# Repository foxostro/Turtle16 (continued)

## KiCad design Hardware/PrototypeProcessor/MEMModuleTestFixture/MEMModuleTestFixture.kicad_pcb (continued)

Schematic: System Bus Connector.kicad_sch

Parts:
J2: 71922-164LF; IDC-Header_2x32_P2.54mm_Horizontal

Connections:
/MEM Prototype Inputs/Phi2: J2.55; also elsewhere on the board
/MEM Prototype Inputs/RDY: J2.59; also elsewhere on the board
/MEM Prototype Inputs/~RST_sync: J2.60; also elsewhere on the board
/System Bus Connector/Addr0: J2.7; also elsewhere on the board
/System Bus Connector/Addr1: J2.8; also elsewhere on the board
/System Bus Connector/Addr2: J2.9; also elsewhere on the board
/System Bus Connector/Addr3: J2.10; also elsewhere on the board
/System Bus Connector/Addr4: J2.13; also elsewhere on the board
/System Bus Connector/Addr5: J2.14; also elsewhere on the board
/System Bus Connector/Addr6: J2.15; also elsewhere on the board
/System Bus Connector/Addr7: J2.16; also elsewhere on the board
/System Bus Connector/Addr8: J2.19; also elsewhere on the board
/System Bus Connector/Addr9: J2.20; also elsewhere on the board
/System Bus Connector/Addr10: J2.21; also elsewhere on the board
/System Bus Connector/Addr11: J2.22; also elsewhere on the board
/System Bus Connector/Addr12: J2.25; also elsewhere on the board
/System Bus Connector/Addr13: J2.26; also elsewhere on the board
/System Bus Connector/Addr14: J2.27; also elsewhere on the board
/System Bus Connector/Addr15: J2.28; also elsewhere on the board
/System Bus Connector/Bank0: J2.56; also elsewhere on the board
/System Bus Connector/Bank1: J2.3; also elsewhere on the board
/System Bus Connector/Bank2: J2.4; also elsewhere on the board
/System Bus Connector/IO0: J2.51; also elsewhere on the board
/System Bus Connector/IO1: J2.52; also elsewhere on the board
/System Bus Connector/IO2: J2.49; also elsewhere on the board
/System Bus Connector/IO3: J2.50; also elsewhere on the board
/System Bus Connector/IO4: J2.45; also elsewhere on the board
/System Bus Connector/IO5: J2.46; also elsewhere on the board
/System Bus Connector/IO6: J2.43; also elsewhere on the board
/System Bus Connector/IO7: J2.44; also elsewhere on the board
/System Bus Connector/IO8: J2.39; also elsewhere on the board
/System Bus Connector/IO9: J2.40; also elsewhere on the board
/System Bus Connector/IO10: J2.37; also elsewhere on the board
/System Bus Connector/IO11: J2.38; also elsewhere on the board
/System Bus Connector/IO12: J2.33; also elsewhere on the board
/System Bus Connector/IO13: J2.34; also elsewhere on the board
/System Bus Connector/IO14: J2.31; also elsewhere on the board
/System Bus Connector/IO15: J2.32; also elsewhere on the board
/System Bus Connector/~MemLoad: J2.62; also elsewhere on the board
/System Bus Connector/~MemStore: J2.61; also elsewhere on the board
GND: J2.1, J2.2, J2.5, J2.6, J2.11, J2.12, J2.17, J2.18, J2.23, J2.24, J2.29, J2.30, J2.35, J2.36, J2.41, J2.42, J2.47, J2.48, J2.53, J2.54, J2.57, J2.58; also elsewhere on the board
VCC: J2.63, J2.64; also elsewhere on the board

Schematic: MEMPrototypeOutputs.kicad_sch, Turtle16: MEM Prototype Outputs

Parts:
J3: StoreOp_WB; PinHeader_1x16_P2.54mm_Vertical
J4: Ins_IF; PinHeader_1x16_P2.54mm_Vertical
J5: SelC_MEM; PinHeader_1x03_P2.54mm_Vertical
J6: Y_WB; PinHeader_1x16_P2.54mm_Vertical
J7: Ctl_MEM; PinHeader_1x04_P2.54mm_Vertical

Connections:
/Ctl_WB17: J7.1; also elsewhere on the board
/Ctl_WB18: J7.2; also elsewhere on the board
/Ctl_WB19: J7.3; also elsewhere on the board
/Ctl_WB20: J7.4; also elsewhere on the board
/Ins_IF0: J4.1; also elsewhere on the board
/Ins_IF1: J4.2; also elsewhere on the board
/Ins_IF2: J4.3; also elsewhere on the board
/Ins_IF3: J4.4; also elsewhere on the board
/Ins_IF4: J4.5; also elsewhere on the board
/Ins_IF5: J4.6; also elsewhere on the board
/Ins_IF6: J4.7; also elsewhere on the board
/Ins_IF7: J4.8; also elsewhere on the board
/Ins_IF8: J4.9; also elsewhere on the board
/Ins_IF9: J4.10; also elsewhere on the board
/Ins_IF10: J4.11; also elsewhere on the board
/Ins_IF11: J4.12; also elsewhere on the board
/Ins_IF12: J4.13; also elsewhere on the board
/Ins_IF13: J4.14; also elsewhere on the board
/Ins_IF14: J4.15; also elsewhere on the board
/Ins_IF15: J4.16; also elsewhere on the board
/SelC_WB0: J5.1; also elsewhere on the board
/SelC_WB1: J5.2; also elsewhere on the board
/SelC_WB2: J5.3; also elsewhere on the board
/StoreOp_WB0: J3.1; also elsewhere on the board
/StoreOp_WB1: J3.2; also elsewhere on the board
/StoreOp_WB2: J3.3; also elsewhere on the board
/StoreOp_WB3: J3.4; also elsewhere on the board
/StoreOp_WB4: J3.5; also elsewhere on the board
/StoreOp_WB5: J3.6; also elsewhere on the board
/StoreOp_WB6: J3.7; also elsewhere on the board
/StoreOp_WB7: J3.8; also elsewhere on the board
/StoreOp_WB8: J3.9; also elsewhere on the board
/StoreOp_WB9: J3.10; also elsewhere on the board
/StoreOp_WB10: J3.11; also elsewhere on the board
/StoreOp_WB11: J3.12; also elsewhere on the board
/StoreOp_WB12: J3.13; also elsewhere on the board
/StoreOp_WB13: J3.14; also elsewhere on the board
/StoreOp_WB14: J3.15; also elsewhere on the board
/StoreOp_WB15: J3.16; also elsewhere on the board
/Y_WB0: J6.1; also elsewhere on the board
/Y_WB1: J6.2; also elsewhere on the board
/Y_WB2: J6.3; also elsewhere on the board
/Y_WB3: J6.4; also elsewhere on the board
/Y_WB4: J6.5; also elsewhere on the board
/Y_WB5: J6.6; also elsewhere on the board
/Y_WB6: J6.7; also elsewhere on the board
/Y_WB7: J6.8; also elsewhere on the board
/Y_WB8: J6.9; also elsewhere on the board
/Y_WB9: J6.10; also elsewhere on the board
/Y_WB10: J6.11; also elsewhere on the board
/Y_WB11: J6.12; also elsewhere on the board
/Y_WB12: J6.13; also elsewhere on the board
/Y_WB13: J6.14; also elsewhere on the board
/Y_WB14: J6.15; also elsewhere on the board
/Y_WB15: J6.16; also elsewhere on the board

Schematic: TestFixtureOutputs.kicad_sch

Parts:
C9, C10, C11, C12, C13, C14, C15, C16, C17, C18: 0.1µF; C_0603_1608Metric
D1, D2, D3, D4, D5, D6, D7, D8: Red; LED_0603_1608Metric
R1, R2, R3, R4, R5, R6, R7, R8: 270R; C_0603_1608Metric
U8, U9, U10, U11, U12, U13, U14, U15, U16: 74HC595; TSSOP-16_4.4x5mm_P0.65mm
U17: 74HCT05; TSSOP-14_4.4x5mm_P0.65mm

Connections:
/Ctl_MEM14: U14.15 (QA); also elsewhere on the board
/Ctl_MEM15: U14.1 (QB); also elsewhere on the board
/Ctl_MEM16: U14.2 (QC); also elsewhere on the board
/Ctl_MEM17: U14.3 (QD); also elsewhere on the board
/Ctl_MEM18: U14.4 (QE); also elsewhere on the board
/Ctl_MEM19: U14.5 (QF); also elsewhere on the board
/Ctl_MEM20: U14.6 (QG); also elsewhere on the board
/MEM Prototype Inputs/FLUSH_IF: U15.15 (QA); also elsewhere on the board
/MEM Prototype Inputs/PC0: U8.15 (QA); also elsewhere on the board
/MEM Prototype Inputs/PC1: U8.1 (QB); also elsewhere on the board
/MEM Prototype Inputs/PC2: U8.2 (QC); also elsewhere on the board
/MEM Prototype Inputs/PC3: U8.3 (QD); also elsewhere on the board
/MEM Prototype Inputs/PC4: U8.4 (QE); also elsewhere on the board
/MEM Prototype Inputs/PC5: U8.5 (QF); also elsewhere on the board
/MEM Prototype Inputs/PC6: U8.6 (QG); also elsewhere on the board
/MEM Prototype Inputs/PC7: U8.7 (QH); also elsewhere on the board
/MEM Prototype Inputs/PC8: U9.15 (QA); also elsewhere on the board
/MEM Prototype Inputs/PC9: U9.1 (QB); also elsewhere on the board
/MEM Prototype Inputs/PC10: U9.2 (QC); also elsewhere on the board
/MEM Prototype Inputs/PC11: U9.3 (QD); also elsewhere on the board
/MEM Prototype Inputs/PC12: U9.4 (QE); also elsewhere on the board
/MEM Prototype Inputs/PC13: U9.5 (QF); also elsewhere on the board
/MEM Prototype Inputs/PC14: U9.6 (QG); also elsewhere on the board
/MEM Prototype Inputs/PC15: U9.7 (QH); also elsewhere on the board
/MEM Prototype Inputs/Phi1b: U15.2 (QC); also elsewhere on the board
/MEM Prototype Inputs/Phi2: U15.1 (QB); also elsewhere on the board
/MEM Prototype Inputs/RDY: U17.2; also elsewhere on the board
/MEM Prototype Inputs/~RST_sync: U15.4 (QE); also elsewhere on the board
/SelC_MEM0: U15.5 (QF); also elsewhere on the board
/SelC_MEM1: U15.6 (QG); also elsewhere on the board
/SelC_MEM2: U15.7 (QH); also elsewhere on the board
/StoreOp_MEM0: U12.15 (QA); also elsewhere on the board
/StoreOp_MEM1: U12.1 (QB); also elsewhere on the board
/StoreOp_MEM2: U12.2 (QC); also elsewhere on the board
/StoreOp_MEM3: U12.3 (QD); also elsewhere on the board
/StoreOp_MEM4: U12.4 (QE); also elsewhere on the board
/StoreOp_MEM5: U12.5 (QF); also elsewhere on the board
/StoreOp_MEM6: U12.6 (QG); also elsewhere on the board
/StoreOp_MEM7: U12.7 (QH); also elsewhere on the board
/StoreOp_MEM8: U13.15 (QA); also elsewhere on the board
/StoreOp_MEM9: U13.1 (QB); also elsewhere on the board
/StoreOp_MEM10: U13.2 (QC); also elsewhere on the board
/StoreOp_MEM11: U13.3 (QD); also elsewhere on the board
/StoreOp_MEM12: U13.4 (QE); also elsewhere on the board
/StoreOp_MEM13: U13.5 (QF); also elsewhere on the board
/StoreOp_MEM14: U13.6 (QG); also elsewhere on the board
/StoreOp_MEM15: U13.7 (QH); also elsewhere on the board
/Test Fixture Outputs/RCLK: U8.12 (RCLK), U9.12 (RCLK), U10.12 (RCLK), U11.12 (RCLK), U12.12 (RCLK), U13.12 (RCLK), U14.12 (RCLK), U15.12 (RCLK), U16.12 (RCLK); also elsewhere on the board
/Test Fixture Outputs/SCK: U8.11 (SRCLK), U9.11 (SRCLK), U10.11 (SRCLK), U11.11 (SRCLK), U12.11 (SRCLK), U13.11 (SRCLK), U14.11 (SRCLK), U15.11 (SRCLK), U16.11 (SRCLK); also elsewhere on the board
/Test Fixture Outputs/SI: U8.14 (SER); also elsewhere on the board
/Test Fixture Outputs/SO: U16.9 (QH')
/Test Fixture Outputs/~CLR: U8.10 (~SRCLR), U9.10 (~SRCLR), U10.10 (~SRCLR), U11.10 (~SRCLR), U12.10 (~SRCLR), U13.10 (~SRCLR), U14.10 (~SRCLR), U15.10 (~SRCLR), U16.10 (~SRCLR); also elsewhere on the board
/Y_MEM0: U10.15 (QA); also elsewhere on the board
/Y_MEM1: U10.1 (QB); also elsewhere on the board
/Y_MEM2: U10.2 (QC); also elsewhere on the board
/Y_MEM3: U10.3 (QD); also elsewhere on the board
/Y_MEM4: U10.4 (QE); also elsewhere on the board
/Y_MEM5: U10.5 (QF); also elsewhere on the board
/Y_MEM6: U10.6 (QG); also elsewhere on the board
/Y_MEM7: U10.7 (QH); also elsewhere on the board
/Y_MEM8: U11.15 (QA); also elsewhere on the board
/Y_MEM9: U11.1 (QB); also elsewhere on the board
/Y_MEM10: U11.2 (QC); also elsewhere on the board
/Y_MEM11: U11.3 (QD); also elsewhere on the board
/Y_MEM12: U11.4 (QE); also elsewhere on the board
/Y_MEM13: U11.5 (QF); also elsewhere on the board
/Y_MEM14: U11.6 (QG); also elsewhere on the board
/Y_MEM15: U11.7 (QH); also elsewhere on the board
GND: C9.2, C10.2, C11.2, C12.2, C13.2, C14.2, C15.2, C16.2, C17.2, C18.2, R1.2, R2.2, R3.2, R4.2, R5.2, R6.2, R7.2, R8.2, U8.8 (GND), U8.13 (~OE), U9.8 (GND), U9.13 (~OE), U10.8 (GND), U10.13 (~OE), U11.8 (GND), U11.13 (~OE), U12.8 (GND), U12.13 (~OE), U13.8 (GND), U13.13 (~OE), U14.8 (GND), U14.13 (~OE), U15.8 (GND), U15.13 (~OE), U16.8 (GND), U16.13 (~OE), U17.7 (GND); also elsewhere on the board
unnamed: D1.2 (A), U16.15 (QA)
unnamed: D1.1 (K), R1.1
unnamed: D2.2 (A), U16.1 (QB)
unnamed: D2.1 (K), R2.1
unnamed: D3.2 (A), U16.2 (QC)
unnamed: D3.1 (K), R3.1
unnamed: D4.2 (A), U16.3 (QD)
unnamed: D4.1 (K), R4.1
unnamed: D5.2 (A), U16.4 (QE)
unnamed: D5.1 (K), R5.1
unnamed: D6.2 (A), U16.5 (QF)
unnamed: D6.1 (K), R6.1
unnamed: D7.2 (A), U16.6 (QG)
unnamed: D7.1 (K), R7.1
unnamed: D8.2 (A), U16.7 (QH)
unnamed: D8.1 (K), R8.1
unnamed: U8.9 (QH'), U9.14 (SER)
unnamed: U10.9 (QH'), U11.14 (SER)
unnamed: U9.9 (QH'), U10.14 (SER)
unnamed: U11.9 (QH'), U12.14 (SER)
unnamed: U12.9 (QH'), U13.14 (SER)
unnamed: U13.9 (QH'), U14.14 (SER)
unnamed: U14.9 (QH'), U15.14 (SER)
unnamed: U15.3 (QD), U17.1
unnamed: U15.9 (QH'), U16.14 (SER)
VCC: C9.1, C10.1, C11.1, C12.1, C13.1, C14.1, C15.1, C16.1, C17.1, C18.1, U8.16 (VCC), U9.16 (VCC), U10.16 (VCC), U11.16 (VCC), U12.16 (VCC), U13.16 (VCC), U14.16 (VCC), U15.16 (VCC), U16.16 (VCC), U17.3, U17.5, U17.9, U17.11, U17.13, U17.14 (VCC); also elsewhere on the board

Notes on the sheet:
RDY is an open-drain line intended to be shared between several modules. It has a pull-up resistor on the MEM module to keep it HIGH when it is not actively being driven LOW.
Test Fixture's Status LEDs

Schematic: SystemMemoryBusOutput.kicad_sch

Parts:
C19, C20, C21, C22, C23, C24, C25: 0.1µF; C_0603_1608Metric
U18, U19, U20, U21, U22, U23, U24: 74HC595; TSSOP-16_4.4x5mm_P0.65mm

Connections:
/System Bus Connector/Addr0: U20.15 (QA); also elsewhere on the board
/System Bus Connector/Addr1: U20.1 (QB); also elsewhere on the board
/System Bus Connector/Addr2: U20.2 (QC); also elsewhere on the board
/System Bus Connector/Addr3: U20.3 (QD); also elsewhere on the board
/System Bus Connector/Addr4: U20.4 (QE); also elsewhere on the board
/System Bus Connector/Addr5: U20.5 (QF); also elsewhere on the board
/System Bus Connector/Addr6: U20.6 (QG); also elsewhere on the board
/System Bus Connector/Addr7: U20.7 (QH); also elsewhere on the board
/System Bus Connector/Addr8: U21.15 (QA); also elsewhere on the board
/System Bus Connector/Addr9: U21.1 (QB); also elsewhere on the board
/System Bus Connector/Addr10: U21.2 (QC); also elsewhere on the board
/System Bus Connector/Addr11: U21.3 (QD); also elsewhere on the board
/System Bus Connector/Addr12: U21.4 (QE); also elsewhere on the board
/System Bus Connector/Addr13: U21.5 (QF); also elsewhere on the board
/System Bus Connector/Addr14: U21.6 (QG); also elsewhere on the board
/System Bus Connector/Addr15: U21.7 (QH); also elsewhere on the board
/System Bus Connector/Bank0: U22.15 (QA); also elsewhere on the board
/System Bus Connector/Bank1: U22.1 (QB); also elsewhere on the board
/System Bus Connector/Bank2: U22.2 (QC); also elsewhere on the board
/System Bus Connector/IO0: U18.15 (QA); also elsewhere on the board
/System Bus Connector/IO1: U18.1 (QB); also elsewhere on the board
/System Bus Connector/IO2: U18.2 (QC); also elsewhere on the board
/System Bus Connector/IO3: U18.3 (QD); also elsewhere on the board
/System Bus Connector/IO4: U18.4 (QE); also elsewhere on the board
/System Bus Connector/IO5: U18.5 (QF); also elsewhere on the board
/System Bus Connector/IO6: U18.6 (QG); also elsewhere on the board
/System Bus Connector/IO7: U18.7 (QH); also elsewhere on the board
/System Bus Connector/IO8: U19.15 (QA); also elsewhere on the board
/System Bus Connector/IO9: U19.1 (QB); also elsewhere on the board
/System Bus Connector/IO10: U19.2 (QC); also elsewhere on the board
/System Bus Connector/IO11: U19.3 (QD); also elsewhere on the board
/System Bus Connector/IO12: U19.4 (QE); also elsewhere on the board
/System Bus Connector/IO13: U19.5 (QF); also elsewhere on the board
/System Bus Connector/IO14: U19.6 (QG); also elsewhere on the board
/System Bus Connector/IO15: U19.7 (QH); also elsewhere on the board
/System Bus Connector/~MemLoad: U23.15 (QA); also elsewhere on the board
/System Bus Connector/~MemStore: U23.1 (QB); also elsewhere on the board
/System Memory Bus Output/OE0: U18.13 (~OE), U24.15 (QA)
/System Memory Bus Output/OE1: U19.13 (~OE), U24.1 (QB)
/System Memory Bus Output/OE2: U20.13 (~OE), U24.2 (QC)
/System Memory Bus Output/OE3: U21.13 (~OE), U24.3 (QD)
/System Memory Bus Output/OE4: U22.13 (~OE), U24.4 (QE)
/System Memory Bus Output/OE5: U23.13 (~OE), U24.5 (QF)
/System Memory Bus Output/RCLK: U18.12 (RCLK), U19.12 (RCLK), U20.12 (RCLK), U21.12 (RCLK), U22.12 (RCLK), U23.12 (RCLK), U24.12 (RCLK); also elsewhere on the board
/System Memory Bus Output/SCK: U18.11 (SRCLK), U19.11 (SRCLK), U20.11 (SRCLK), U21.11 (SRCLK), U22.11 (SRCLK), U23.11 (SRCLK), U24.11 (SRCLK); also elsewhere on the board
/System Memory Bus Output/SI: U18.14 (SER); also elsewhere on the board
/System Memory Bus Output/SO: U24.9 (QH')
/System Memory Bus Output/~CLR: U18.10 (~SRCLR), U19.10 (~SRCLR), U20.10 (~SRCLR), U21.10 (~SRCLR), U22.10 (~SRCLR), U23.10 (~SRCLR), U24.10 (~SRCLR); also elsewhere on the board
GND: C19.2, C20.2, C21.2, C22.2, C23.2, C24.2, C25.2, U18.8 (GND), U19.8 (GND), U20.8 (GND), U21.8 (GND), U22.8 (GND), U23.8 (GND), U24.8 (GND), U24.13 (~OE); also elsewhere on the board
unnamed: U18.9 (QH'), U19.14 (SER)
unnamed: U19.9 (QH'), U20.14 (SER)
unnamed: U20.9 (QH'), U21.14 (SER)
unnamed: U21.9 (QH'), U22.14 (SER)
unnamed: U22.9 (QH'), U23.14 (SER)
unnamed: U23.9 (QH'), U24.14 (SER)
VCC: C19.1, C20.1, C21.1, C22.1, C23.1, C24.1, C25.1, U18.16 (VCC), U19.16 (VCC), U20.16 (VCC), U21.16 (VCC), U22.16 (VCC), U23.16 (VCC), U24.16 (VCC); also elsewhere on the board

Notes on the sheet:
This register controls the output state of the other registers this chain. Registers may be set to either an Output state or a High Impedence state.

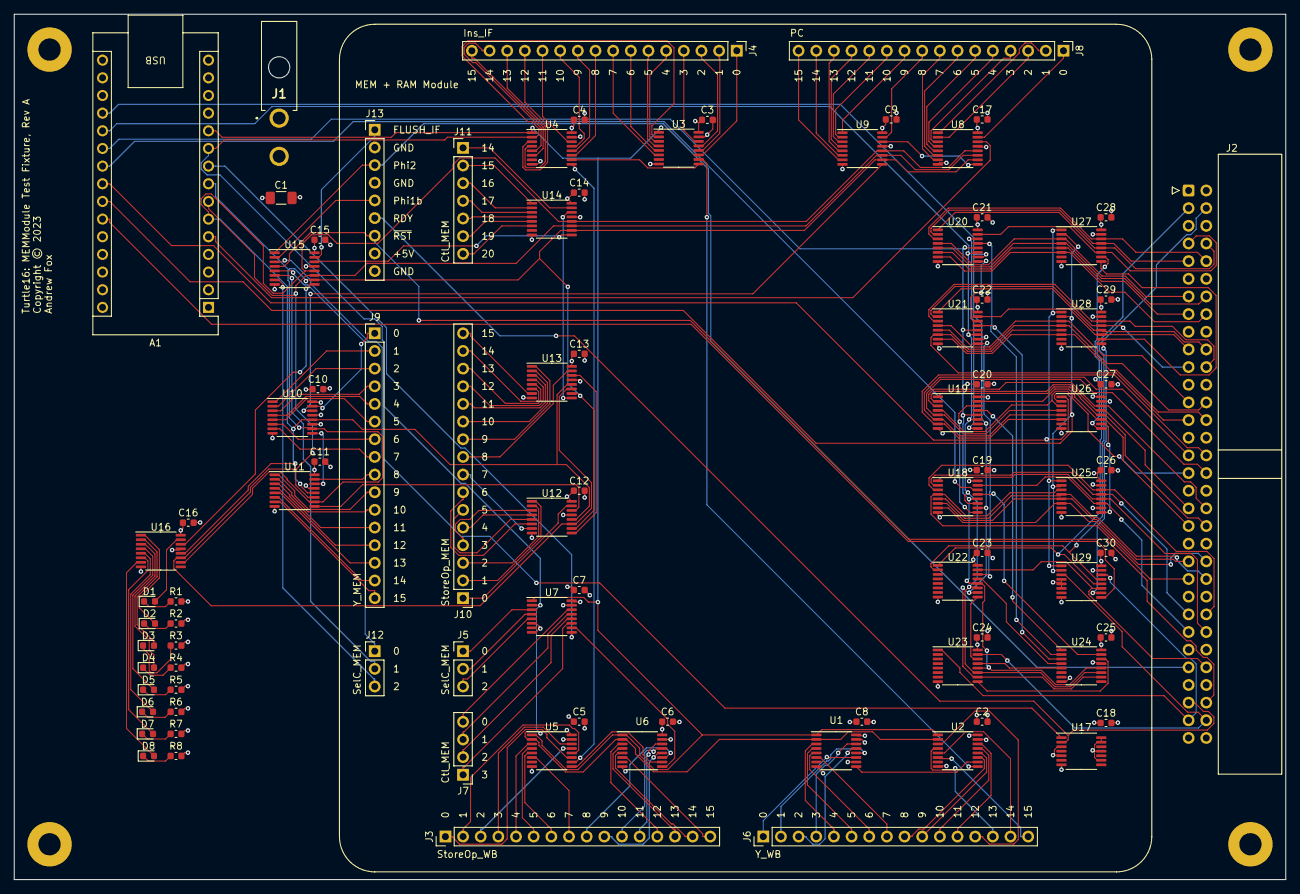
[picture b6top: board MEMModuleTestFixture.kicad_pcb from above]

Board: 4 copper layers, 182.9 x 124.5 mm, 93 parts (0 on the bottom side), 218 nets.

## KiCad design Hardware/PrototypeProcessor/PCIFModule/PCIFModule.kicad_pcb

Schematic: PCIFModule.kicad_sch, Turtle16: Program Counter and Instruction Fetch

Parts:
C1: 100µF; C_1206_3216Metric_Pad1.33x1.80mm_HandSolder
H1, H2, H3, H4: MountingHole_Pad; MountingHole_3.2mm_M3_Pad
J1: Y_EX; PinHeader_1x16_P2.54mm_Vertical
J2: Control Signals; PinHeader_1x08_P2.54mm_Vertical
J3: PC; PinHeader_1x16_P2.54mm_Vertical
J4: FLUSH_IF; PinHeader_1x01_P2.54mm_Vertical
J5: Ins_IF; PinHeader_1x16_P2.54mm_Vertical
J6: Ins_ID; PinHeader_1x16_P2.54mm_Vertical
J7: PC_EX; PinHeader_1x16_P2.54mm_Vertical

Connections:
/IF/FLUSH_IF: J4.1; also elsewhere on the board
/IF/Ins_ID0: J6.1; also elsewhere on the board
/IF/Ins_ID1: J6.2; also elsewhere on the board
/IF/Ins_ID2: J6.3; also elsewhere on the board
/IF/Ins_ID3: J6.4; also elsewhere on the board
/IF/Ins_ID4: J6.5; also elsewhere on the board
/IF/Ins_ID5: J6.6; also elsewhere on the board
/IF/Ins_ID6: J6.7; also elsewhere on the board
/IF/Ins_ID7: J6.8; also elsewhere on the board
/IF/Ins_ID8: J6.9; also elsewhere on the board
/IF/Ins_ID9: J6.10; also elsewhere on the board
/IF/Ins_ID10: J6.11; also elsewhere on the board
/IF/Ins_ID11: J6.12; also elsewhere on the board
/IF/Ins_ID12: J6.13; also elsewhere on the board
/IF/Ins_ID13: J6.14; also elsewhere on the board
/IF/Ins_ID14: J6.15; also elsewhere on the board
/IF/Ins_ID15: J6.16; also elsewhere on the board
/IF/Ins_IF0: J5.1; also elsewhere on the board
/IF/Ins_IF1: J5.2; also elsewhere on the board
/IF/Ins_IF2: J5.3; also elsewhere on the board
/IF/Ins_IF3: J5.4; also elsewhere on the board
/IF/Ins_IF4: J5.5; also elsewhere on the board
/IF/Ins_IF5: J5.6; also elsewhere on the board
/IF/Ins_IF6: J5.7; also elsewhere on the board
/IF/Ins_IF7: J5.8; also elsewhere on the board
/IF/Ins_IF8: J5.9; also elsewhere on the board
/IF/Ins_IF9: J5.10; also elsewhere on the board
/IF/Ins_IF10: J5.11; also elsewhere on the board
/IF/Ins_IF11: J5.12; also elsewhere on the board
/IF/Ins_IF12: J5.13; also elsewhere on the board
/IF/Ins_IF13: J5.14; also elsewhere on the board
/IF/Ins_IF14: J5.15; also elsewhere on the board
/IF/Ins_IF15: J5.16; also elsewhere on the board
/IF/PC_EX0: J7.1; also elsewhere on the board
/IF/PC_EX1: J7.2; also elsewhere on the board
/IF/PC_EX2: J7.3; also elsewhere on the board
/IF/PC_EX3: J7.4; also elsewhere on the board
/IF/PC_EX4: J7.5; also elsewhere on the board
/IF/PC_EX5: J7.6; also elsewhere on the board
/IF/PC_EX6: J7.7; also elsewhere on the board
/IF/PC_EX7: J7.8; also elsewhere on the board
/IF/PC_EX8: J7.9; also elsewhere on the board
/IF/PC_EX9: J7.10; also elsewhere on the board
/IF/PC_EX10: J7.11; also elsewhere on the board
/IF/PC_EX11: J7.12; also elsewhere on the board
/IF/PC_EX12: J7.13; also elsewhere on the board
/IF/PC_EX13: J7.14; also elsewhere on the board
/IF/PC_EX14: J7.15; also elsewhere on the board
/IF/PC_EX15: J7.16; also elsewhere on the board
/IF/Phi1a: J2.2; also elsewhere on the board
/IF/STALL: J2.6; also elsewhere on the board
/IF/Y_EX0: J1.1; also elsewhere on the board
/IF/Y_EX1: J1.2; also elsewhere on the board
/IF/Y_EX2: J1.3; also elsewhere on the board
/IF/Y_EX3: J1.4; also elsewhere on the board
/IF/Y_EX4: J1.5; also elsewhere on the board
/IF/Y_EX5: J1.6; also elsewhere on the board
/IF/Y_EX6: J1.7; also elsewhere on the board
/IF/Y_EX7: J1.8; also elsewhere on the board
/IF/Y_EX8: J1.9; also elsewhere on the board
/IF/Y_EX9: J1.10; also elsewhere on the board
/IF/Y_EX10: J1.11; also elsewhere on the board
/IF/Y_EX11: J1.12; also elsewhere on the board
/IF/Y_EX12: J1.13; also elsewhere on the board
/IF/Y_EX13: J1.14; also elsewhere on the board
/IF/Y_EX14: J1.15; also elsewhere on the board
/IF/Y_EX15: J1.16; also elsewhere on the board
/IF/sheet5FE3DA15/PC0: J3.1; also elsewhere on the board
/IF/sheet5FE3DA15/PC1: J3.2; also elsewhere on the board
/IF/sheet5FE3DA15/PC2: J3.3; also elsewhere on the board
/IF/sheet5FE3DA15/PC3: J3.4; also elsewhere on the board
/IF/sheet5FE3DA15/PC4: J3.5; also elsewhere on the board
/IF/sheet5FE3DA15/PC5: J3.6; also elsewhere on the board
/IF/sheet5FE3DA15/PC6: J3.7; also elsewhere on the board
/IF/sheet5FE3DA15/PC7: J3.8; also elsewhere on the board
/IF/sheet5FE3DA15/PC8: J3.9; also elsewhere on the board
/IF/sheet5FE3DA15/PC9: J3.10; also elsewhere on the board
/IF/sheet5FE3DA15/PC10: J3.11; also elsewhere on the board
/IF/sheet5FE3DA15/PC11: J3.12; also elsewhere on the board
/IF/sheet5FE3DA15/PC12: J3.13; also elsewhere on the board
/IF/sheet5FE3DA15/PC13: J3.14; also elsewhere on the board
/IF/sheet5FE3DA15/PC14: J3.15; also elsewhere on the board
/IF/sheet5FE3DA15/PC15: J3.16; also elsewhere on the board
/IF/~JABS: J2.5; also elsewhere on the board
/IF/~J: J2.4; also elsewhere on the board
/IF/~RST_sync: J2.3; also elsewhere on the board
GND: C1.2, H1.1, H2.1, H3.1, H4.1, J2.1, J2.8; also elsewhere on the board
VCC: C1.1, J2.7; also elsewhere on the board

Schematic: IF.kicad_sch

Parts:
R1, R2, R3, R4, R5, R6, R7, R8, R9, R10, R11, R12, R13, R14, R15, R16: 10K; R_0603_1608Metric_Pad0.98x0.95mm_HandSolder

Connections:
/IF/Ins_IF0: R1.1; also elsewhere on the board
/IF/Ins_IF1: R2.1; also elsewhere on the board
/IF/Ins_IF2: R3.1; also elsewhere on the board
/IF/Ins_IF3: R4.1; also elsewhere on the board
/IF/Ins_IF4: R5.1; also elsewhere on the board
/IF/Ins_IF5: R6.1; also elsewhere on the board
/IF/Ins_IF6: R7.1; also elsewhere on the board
/IF/Ins_IF7: R8.1; also elsewhere on the board
/IF/Ins_IF8: R9.1; also elsewhere on the board
/IF/Ins_IF9: R10.1; also elsewhere on the board
/IF/Ins_IF10: R11.1; also elsewhere on the board
/IF/Ins_IF11: R12.1; also elsewhere on the board
/IF/Ins_IF12: R13.1; also elsewhere on the board
/IF/Ins_IF13: R14.1; also elsewhere on the board
/IF/Ins_IF14: R15.1; also elsewhere on the board
/IF/Ins_IF15: R16.1; also elsewhere on the board
GND: R1.2, R2.2, R3.2, R4.2, R5.2, R6.2, R7.2, R8.2, R9.2, R10.2, R11.2, R12.2, R13.2, R14.2, R15.2, R16.2; also elsewhere on the board

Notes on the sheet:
Instruction RAM
When the IF stage is flushed, all the output lines are pulled low. This configuration represents a NOP.

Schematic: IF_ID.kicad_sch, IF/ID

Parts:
C5, C6, C7: 100nF; C_0603_1608Metric_Pad1.08x0.95mm_HandSolder
TP3: CLK; TestPoint_Pad_D1.0mm
U4: 74ABT32; TSSOP-14_4.4x5mm_P0.65mm
U5, U6: 74ABT16374; TSSOP-48_8x12.5mm_P0.5mm

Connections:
/IF/Ins_ID0: U6.2 (1Q1); also elsewhere on the board
/IF/Ins_ID1: U6.3 (1Q2); also elsewhere on the board
/IF/Ins_ID2: U6.5 (1Q3); also elsewhere on the board
/IF/Ins_ID3: U6.6 (1Q4); also elsewhere on the board
/IF/Ins_ID4: U6.8 (1Q5); also elsewhere on the board
/IF/Ins_ID5: U6.9 (1Q6); also elsewhere on the board
/IF/Ins_ID6: U6.11 (1Q7); also elsewhere on the board
/IF/Ins_ID7: U6.12 (1Q8); also elsewhere on the board
/IF/Ins_ID8: U6.13 (2Q1); also elsewhere on the board
/IF/Ins_ID9: U6.14 (2Q2); also elsewhere on the board
/IF/Ins_ID10: U6.16 (2Q3); also elsewhere on the board
/IF/Ins_ID11: U6.17 (2Q4); also elsewhere on the board
/IF/Ins_ID12: U6.19 (2Q5); also elsewhere on the board
/IF/Ins_ID13: U6.20 (2Q6); also elsewhere on the board
/IF/Ins_ID14: U6.22 (2Q7); also elsewhere on the board
/IF/Ins_ID15: U6.23 (2Q8); also elsewhere on the board
/IF/Ins_IF0: U6.47 (1D1); also elsewhere on the board
/IF/Ins_IF1: U6.46 (1D2); also elsewhere on the board
/IF/Ins_IF2: U6.44 (1D3); also elsewhere on the board
/IF/Ins_IF3: U6.43 (1D4); also elsewhere on the board
/IF/Ins_IF4: U6.41 (1D5); also elsewhere on the board
/IF/Ins_IF5: U6.40 (1D6); also elsewhere on the board
/IF/Ins_IF6: U6.38 (1D7); also elsewhere on the board
/IF/Ins_IF7: U6.37 (1D8); also elsewhere on the board
/IF/Ins_IF8: U6.36 (2D1); also elsewhere on the board
/IF/Ins_IF9: U6.35 (2D2); also elsewhere on the board
/IF/Ins_IF10: U6.33 (2D3); also elsewhere on the board
/IF/Ins_IF11: U6.32 (2D4); also elsewhere on the board
/IF/Ins_IF12: U6.30 (2D5); also elsewhere on the board
/IF/Ins_IF13: U6.29 (2D6); also elsewhere on the board
/IF/Ins_IF14: U6.27 (2D7); also elsewhere on the board
/IF/Ins_IF15: U6.26 (2D8); also elsewhere on the board
/IF/PC_EX0: U5.2 (1Q1); also elsewhere on the board
/IF/PC_EX1: U5.3 (1Q2); also elsewhere on the board
/IF/PC_EX2: U5.5 (1Q3); also elsewhere on the board
/IF/PC_EX3: U5.6 (1Q4); also elsewhere on the board
/IF/PC_EX4: U5.8 (1Q5); also elsewhere on the board
/IF/PC_EX5: U5.9 (1Q6); also elsewhere on the board
/IF/PC_EX6: U5.11 (1Q7); also elsewhere on the board
/IF/PC_EX7: U5.12 (1Q8); also elsewhere on the board
/IF/PC_EX8: U5.13 (2Q1); also elsewhere on the board
/IF/PC_EX9: U5.14 (2Q2); also elsewhere on the board
/IF/PC_EX10: U5.16 (2Q3); also elsewhere on the board
/IF/PC_EX11: U5.17 (2Q4); also elsewhere on the board
/IF/PC_EX12: U5.19 (2Q5); also elsewhere on the board
/IF/PC_EX13: U5.20 (2Q6); also elsewhere on the board
/IF/PC_EX14: U5.22 (2Q7); also elsewhere on the board
/IF/PC_EX15: U5.23 (2Q8); also elsewhere on the board
/IF/Phi1a: U4.1; also elsewhere on the board
/IF/STALL: U4.2; also elsewhere on the board
/IF/sheet5FE3DA15/PC0: U5.47 (1D1); also elsewhere on the board
/IF/sheet5FE3DA15/PC1: U5.46 (1D2); also elsewhere on the board
/IF/sheet5FE3DA15/PC2: U5.44 (1D3); also elsewhere on the board
/IF/sheet5FE3DA15/PC3: U5.43 (1D4); also elsewhere on the board
/IF/sheet5FE3DA15/PC4: U5.41 (1D5); also elsewhere on the board
/IF/sheet5FE3DA15/PC5: U5.40 (1D6); also elsewhere on the board
/IF/sheet5FE3DA15/PC6: U5.38 (1D7); also elsewhere on the board
/IF/sheet5FE3DA15/PC7: U5.37 (1D8); also elsewhere on the board
/IF/sheet5FE3DA15/PC8: U5.36 (2D1); also elsewhere on the board
/IF/sheet5FE3DA15/PC9: U5.35 (2D2); also elsewhere on the board
/IF/sheet5FE3DA15/PC10: U5.33 (2D3); also elsewhere on the board
/IF/sheet5FE3DA15/PC11: U5.32 (2D4); also elsewhere on the board
/IF/sheet5FE3DA15/PC12: U5.30 (2D5); also elsewhere on the board
/IF/sheet5FE3DA15/PC13: U5.29 (2D6); also elsewhere on the board
/IF/sheet5FE3DA15/PC14: U5.27 (2D7); also elsewhere on the board
/IF/sheet5FE3DA15/PC15: U5.26 (2D8); also elsewhere on the board
GND: C5.2, C6.2, C7.2, U4.7 (GND), U5.1 (1~OE), U5.4 (GND), U5.10 (GND), U5.15 (GND), U5.21 (GND), U5.24 (2~OE), U5.28 (GND), U5.34 (GND), U5.39 (GND), U5.45 (GND), U6.1 (1~OE), U6.4 (GND), U6.10 (GND), U6.15 (GND), U6.21 (GND), U6.24 (2~OE), U6.28 (GND), U6.34 (GND), U6.39 (GND), U6.45 (GND); also elsewhere on the board
unnamed: TP3.1, U4.3, U5.25 (2CLK), U5.48 (1CLK), U6.25 (2CLK), U6.48 (1CLK)
VCC: C5.1, C6.1, C7.1, U4.4, U4.5, U4.9, U4.10, U4.12, U4.13, U4.14 (VCC), U5.7 (VCC), U5.18 (VCC), U5.31 (VCC), U5.42 (VCC), U6.7 (VCC), U6.18 (VCC), U6.31 (VCC), U6.42 (VCC); also elsewhere on the board

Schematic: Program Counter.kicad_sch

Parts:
C2, C3, C4: 100nF; C_0603_1608Metric_Pad1.08x0.95mm_HandSolder
TP1: TP; TestPoint_Pad_D1.0mm
TP2: RS1; TestPoint_Pad_D1.0mm
U1: 74ABT32; TSSOP-14_4.4x5mm_P0.65mm
U2: 74AHCT04; TSSOP-14_4.4x5mm_P0.65mm
U3: IDT7381; PLCC-68_SMD-Socket

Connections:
/IF/FLUSH_IF: U1.3; also elsewhere on the board
/IF/Phi1a: U3.17 (CLK); also elsewhere on the board
/IF/STALL: U3.25 (~ENF); also elsewhere on the board
/IF/Y_EX0: U3.53 (B0); also elsewhere on the board
/IF/Y_EX1: U3.54 (B1); also elsewhere on the board
/IF/Y_EX2: U3.55 (B2); also elsewhere on the board
/IF/Y_EX3: U3.56 (B3); also elsewhere on the board
/IF/Y_EX4: U3.57 (B4); also elsewhere on the board
/IF/Y_EX5: U3.58 (B5); also elsewhere on the board
/IF/Y_EX6: U3.59 (B6); also elsewhere on the board
/IF/Y_EX7: U3.60 (B7); also elsewhere on the board
/IF/Y_EX8: U3.61 (B8); also elsewhere on the board
/IF/Y_EX9: U3.62 (B9); also elsewhere on the board
/IF/Y_EX10: U3.63 (B10); also elsewhere on the board
/IF/Y_EX11: U3.64 (B11); also elsewhere on the board
/IF/Y_EX12: U3.65 (B12); also elsewhere on the board
/IF/Y_EX13: U3.66 (B13); also elsewhere on the board
/IF/Y_EX14: U3.67 (B14); also elsewhere on the board
/IF/Y_EX15: U3.68 (B15); also elsewhere on the board
/IF/sheet5FE3DA15/PC0: U3.1 (A0), U3.43 (F0); also elsewhere on the board
/IF/sheet5FE3DA15/PC1: U3.2 (A1), U3.42 (F1); also elsewhere on the board
/IF/sheet5FE3DA15/PC2: U3.3 (A2), U3.41 (F2); also elsewhere on the board
/IF/sheet5FE3DA15/PC3: U3.4 (A3), U3.40 (F3); also elsewhere on the board
/IF/sheet5FE3DA15/PC4: U3.5 (A4), U3.39 (F4); also elsewhere on the board
/IF/sheet5FE3DA15/PC5: U3.6 (A5), U3.38 (F5); also elsewhere on the board
/IF/sheet5FE3DA15/PC6: U3.7 (A6), U3.37 (F6); also elsewhere on the board
/IF/sheet5FE3DA15/PC7: U3.8 (A7), U3.36 (F7); also elsewhere on the board
/IF/sheet5FE3DA15/PC8: U3.9 (A8), U3.35 (F8); also elsewhere on the board
/IF/sheet5FE3DA15/PC9: U3.10 (A9), U3.34 (F9); also elsewhere on the board
/IF/sheet5FE3DA15/PC10: U3.11 (A10), U3.33 (F10); also elsewhere on the board
/IF/sheet5FE3DA15/PC11: U3.12 (A11), U3.32 (F11); also elsewhere on the board
/IF/sheet5FE3DA15/PC12: U3.13 (A12), U3.31 (F12); also elsewhere on the board
/IF/sheet5FE3DA15/PC13: U3.14 (A13), U3.30 (F13); also elsewhere on the board
/IF/sheet5FE3DA15/PC14: U3.15 (A14), U3.29 (F14); also elsewhere on the board
/IF/sheet5FE3DA15/PC15: U3.16 (A15), U3.28 (F15); also elsewhere on the board
/IF/~JABS: U3.48 (RS0); also elsewhere on the board
/IF/~J: U2.1, U3.44 (C0); also elsewhere on the board
/IF/~RST_sync: U2.3, U3.45 (I0), U3.46 (I1); also elsewhere on the board
GND: C2.2, C3.2, C4.2, U1.7 (GND), U2.7 (GND), U3.19 (GND), U3.26 (FTF), U3.27 (~OE), U3.47 (I2); also elsewhere on the board
unnamed: TP1.1, U1.2, U2.4
unnamed: TP2.1, U1.1, U2.2, U3.49 (RS1)
VCC: C2.1, C3.1, C4.1, U1.4, U1.5, U1.9, U1.10, U1.12, U1.13, U1.14 (VCC), U2.5, U2.9, U2.11, U2.13, U2.14 (VCC), U3.18 (VCC), U3.50 (FTAB), U3.51 (~ENB), U3.52 (~ENA); also elsewhere on the board

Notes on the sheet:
Stall the program counter by disabling the update of the IDT7381’s F register.
Flush the IF stage on Jump and on Reset. The flush during Reset ensures the pipeline is filled with NOPs.
Configure the ALU for FTAB=1 and FTF=0. This causes the A and B registers to by bypassed entirely. The F output updates on the next rising edge of the clock. During reset, set the ALU to I2=0, I1=0, I0=0. This causes the ALU to compute a zero and latch it in A on the rising edge of the clock regard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

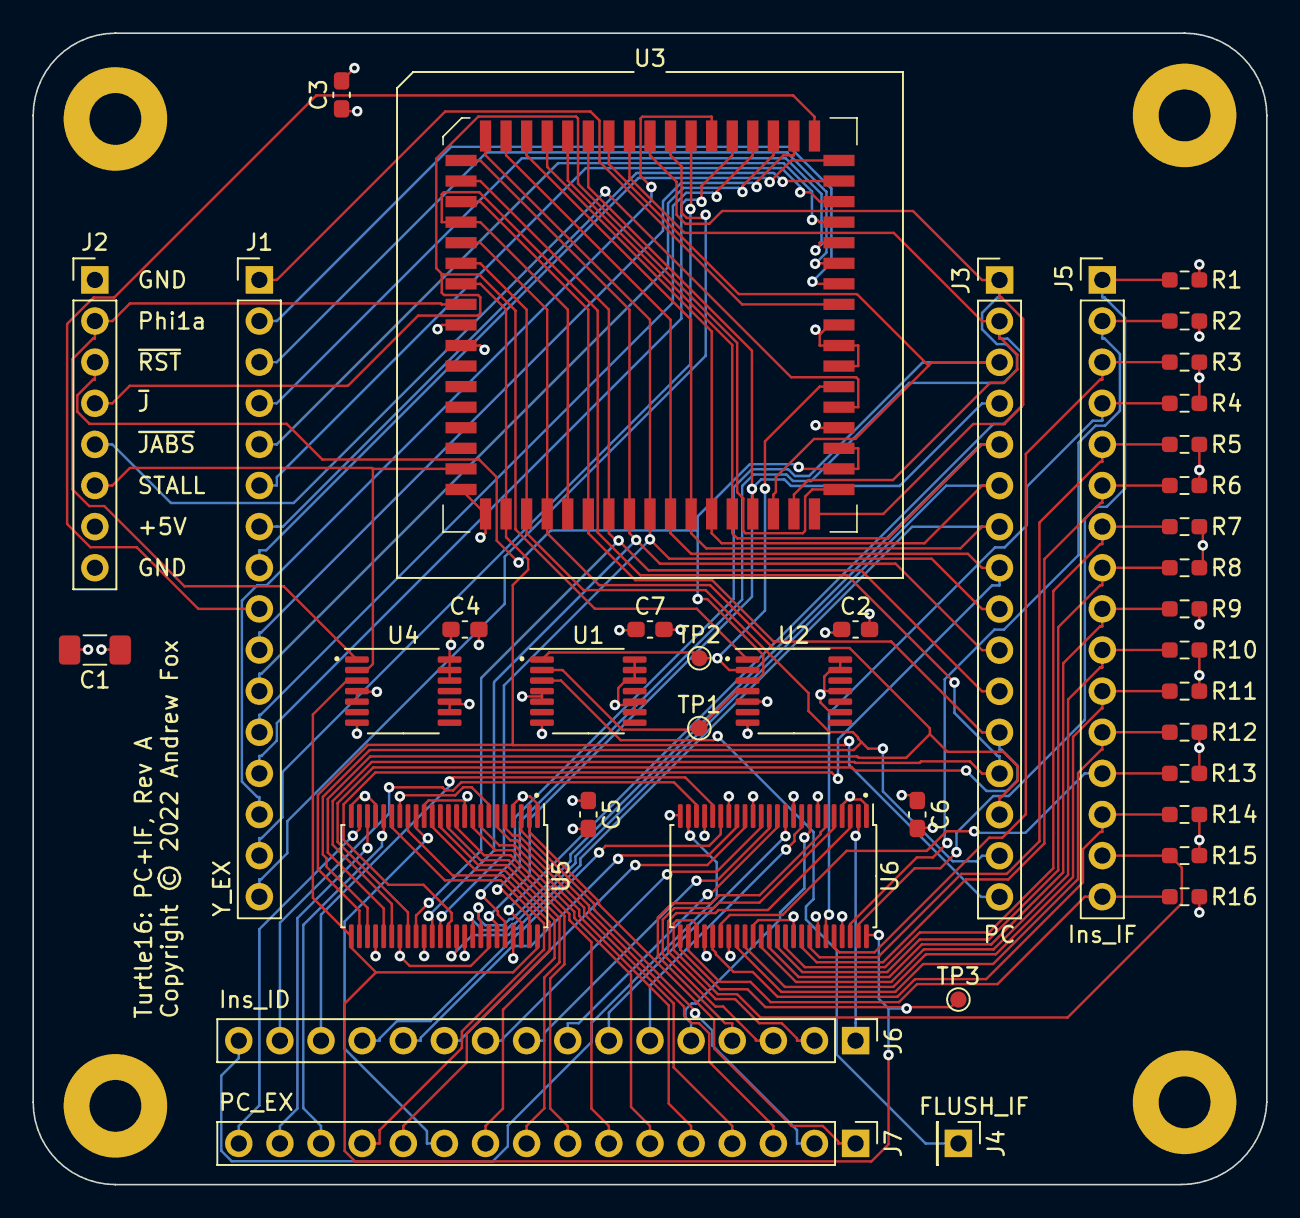
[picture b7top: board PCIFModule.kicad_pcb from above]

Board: 4 copper layers, 76.2 x 71.1 mm, 43 parts (0 on the bottom side), 91 nets.
